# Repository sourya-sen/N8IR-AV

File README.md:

The N8IR is a standalone experimental audiovisual synthesizer and phrase generator. Designed with a simple set of interconnected audio and visual controls and a modular patchbay, the N8IR creates tightly synced audiovisual patterns, powered by a Teensy microcontroller and CMOS logic chips.

Detailed manual and documentation to follow.

This project would not be possible without the knowledge shared on the electro-music forums and previous work by Andy Murkin.

More on Lunetta Synthesis: https://hackaday.com/series_of_posts/logic-noise/ <br>
The Melody Generator Circuit on the electro-music forums: https://electro-music.com/forum/topic-42552.html<br>
Andy Murkin’s delay circuit: https://andymurkin.wordpress.com/2018/03/19/piezos-electrets-pt-4-electronics-and-a-very-very-simple-pt2399-echo-delay/<br>

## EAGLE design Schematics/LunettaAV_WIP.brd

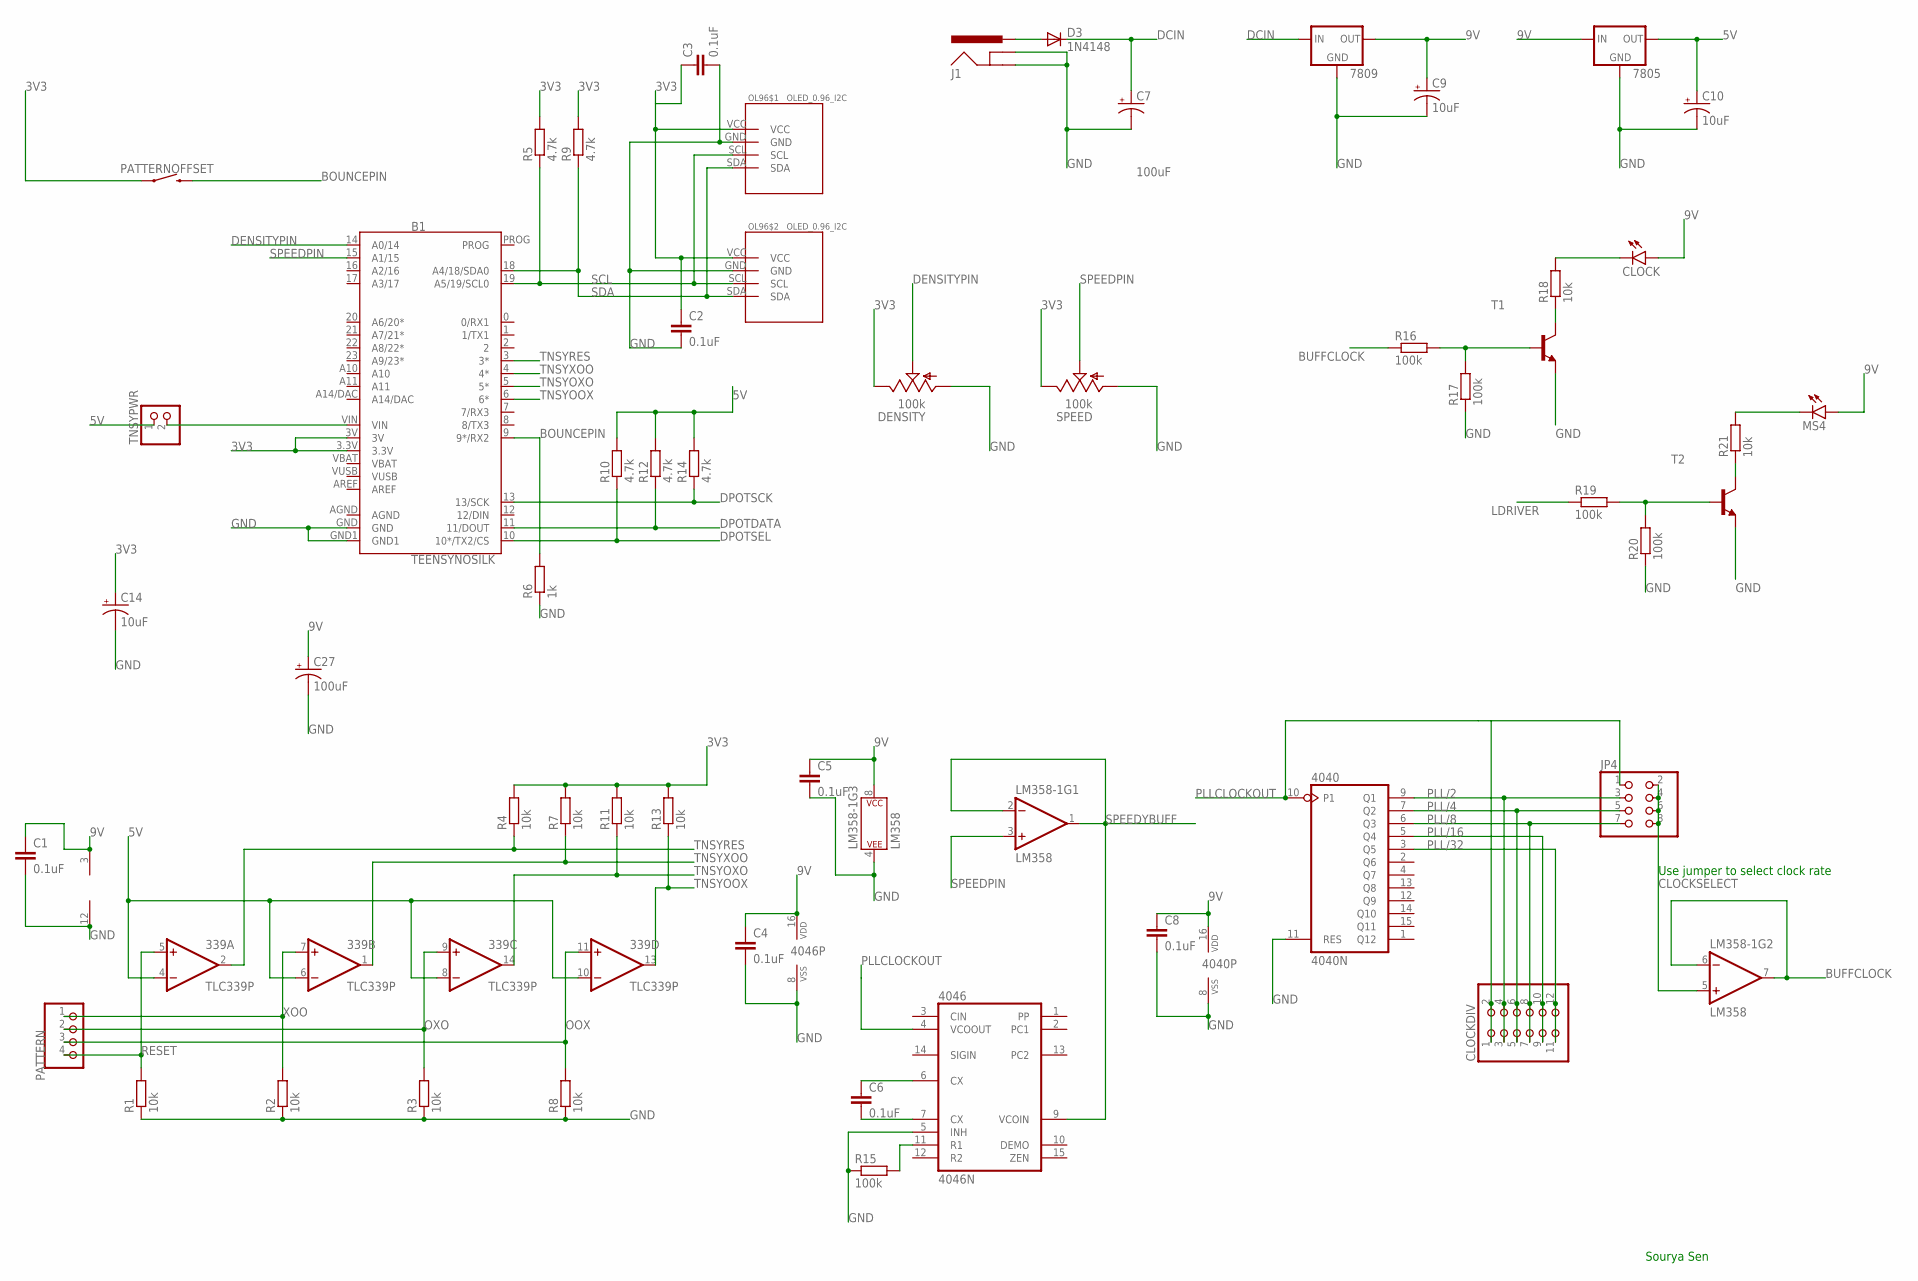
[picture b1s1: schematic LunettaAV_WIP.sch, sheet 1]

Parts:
339: TLC339P; DIL14
4040: 4040N; DIL16
4046: 4046N; DIL16
7805: 7805; 78XXS
7809: 7809; 78XXS
B1: TEENSYNOSILK; TEENSY_NOSILK
C1, C2, C3, C4, C5, C6, C8: 0.1uF; CAP-PTH-SMALL-KIT
C7, C27: 100uF; CPOL-RADIAL-2.5MM-6.5MM
C9, C10, C14: 10uF; CPOL-RADIAL-2.5MM-5MM
CLOCK: LED3MM; LED_3MM
CLOCKDIV: PINHD-2X6; 2X06
D3: 1N4148; DO35-7
DENSITY: 100k; 9MM_SNAP-IN_POT
J1: POWER_JACKPOWER_JACK_SLOT; POWER_JACK_PTH_SLOT
JP4: PINHD-2X4; 2X04
LM358-1: LM358; DIP08
MS4: LED3MM; LED_3MM
OL96$1, OL96$2: OLED_0.96_I2C
PATTERN: PINHD-1X4; 1X04
PATTERNOFFSET: MOMENTARY-SWITCH-SPST-PTH-12MM; TACTILE_SWITCH_PTH_12MM
R1, R2, R3, R4, R7, R8, R11, R13, R18, R21: 10k; 7MM_RESISTOR
R5, R9, R10, R12, R14: 4.7k; 7MM_RESISTOR
R6: 1k; 7MM_RESISTOR
R15, R16, R17, R19, R20: 100k; 7MM_RESISTOR
SPEED: 100k; 9MM_SNAP-IN_POT
T1, T2: 2N4401-NPN-TO92-EBC; TO92-EBC
TNSYPWR: PINHD-1X2; 1X02

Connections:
3V3: B1.3.3V, B1.3V, C2.1, C3.1, C14.1 (+), DENSITY.3 (E), OL96$1.VCC, OL96$2.VCC, PATTERNOFFSET.1, R4.2, R5.2, R7.2, R9.2, R11.2, R13.2, SPEED.3 (E)
5V: 339.4 (-IN), 339.6 (-IN), 339.8 (-IN), 339.10 (-IN), 7805.OUT, C10.1 (+), R10.2, R12.2, R14.2, TNSYPWR.1; also elsewhere on the board
9V: 339.3 (V+), 4040.16 (VDD), 4046.16 (VDD), 7805.IN, 7809.OUT, C1.1, C4.1, C5.1, C8.1, C9.1 (+), C27.1 (+), CLOCK.A, LM358-1.8 (P$V+), MS4.A; also elsewhere on the board
AGND: B1.AGND
BOUNCEPIN: B1.9 (9*/RX2), PATTERNOFFSET.3 (2), R6.2
BUFFCLOCK: LM358-1.6 (-IN), LM358-1.7 (OUT), R16.1; also elsewhere on the board
CLOCKSELECT: JP4.2, JP4.4, JP4.6, JP4.8, LM358-1.5 (+IN)
DCIN: 7809.IN, C7.1 (+), D3.C
DENSITYPIN: B1.14 (A0/14), DENSITY.2 (S)
DPOTDATA: B1.11 (11/DOUT), R12.1; also elsewhere on the board
DPOTSCK: B1.13 (13/SCK), R14.1; also elsewhere on the board
DPOTSEL: B1.10 (10*/TX2/CS), R10.1; also elsewhere on the board
GND: 339.12 (V-), 4040.8 (VSS), 4040.11 (RES), 4046.5 (INH), 4046.8 (VSS), 7805.GND, 7809.GND, B1.GND, B1.GND1, C1.2, C2.2, C3.2, C4.2, C5.2, C7.2 (-), C8.2, C9.2 (-), C10.2 (-), C14.2 (-), C27.2 (-), DENSITY.1 (A), J1.GND, J1.GNDBREAK, LM358-1.4 (P$V-), OL96$1.GND, OL96$2.GND, R1.1, R2.1, R3.1, R6.1, R8.1, R15.1, R17.1, R20.1, SPEED.1 (A), T1.E, T2.E; also elsewhere on the board
LDRIVER: R19.1; also elsewhere on the board
unnamed: B1.VIN, TNSYPWR.2
unnamed: 4046.7 (CX), C6.2
unnamed: 4046.6 (CX), C6.1
unnamed: 4046.11 (R1), R15.2
unnamed: R16.2, R17.2, T1.B
unnamed: R18.1, T1.C
unnamed: CLOCK.K (C), R18.2
unnamed: R19.2, R20.2, T2.B
unnamed: R21.1, T2.C
unnamed: MS4.K (C), R21.2
unnamed: D3.A, J1.PWR
OOX: 339.11 (+IN), PATTERN.3, R8.2
OXO: 339.9 (+IN), PATTERN.2, R3.2
PLL/2: 4040.9 (Q1), CLOCKDIV.3, CLOCKDIV.4, JP4.3
PLL/4: 4040.7 (Q2), CLOCKDIV.5, CLOCKDIV.6, JP4.5
PLL/8: 4040.6 (Q3), CLOCKDIV.7, CLOCKDIV.8, JP4.7
PLL/16: 4040.5 (Q4), CLOCKDIV.9, CLOCKDIV.10
PLL/32: 4040.3 (Q5), CLOCKDIV.11, CLOCKDIV.12
PLLCLOCKOUT: 4040.10 (P1), 4046.4 (VCOOUT), CLOCKDIV.1, CLOCKDIV.2, JP4.1
RESET: 339.5 (+IN), PATTERN.4, R1.2
SCL: B1.19 (A5/19/SCL0), OL96$1.SCL, OL96$2.SCL, R5.1
SDA: B1.18 (A4/18/SDA0), OL96$1.SDA, OL96$2.SDA, R9.1
SPEEDPIN: B1.15 (A1/15), LM358-1.3 (+IN), SPEED.2 (S)
SPEEDYBUFF: 4046.9 (VCOIN), LM358-1.1 (OUT), LM358-1.2 (-IN)
TNSYOOX: 339.13 (OUT), B1.6 (6*), R13.1
TNSYOXO: 339.14 (OUT), B1.5 (5*), R11.1
TNSYRES: 339.2 (OUT), B1.3 (3*), R4.1
TNSYXOO: 339.1 (OUT), B1.4 (4*), R7.1
VBAT: B1.VBAT
VUSB: B1.VUSB
XOO: 339.7 (+IN), PATTERN.1, R2.2

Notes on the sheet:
Use jumper to select clock rate
Sourya Sen

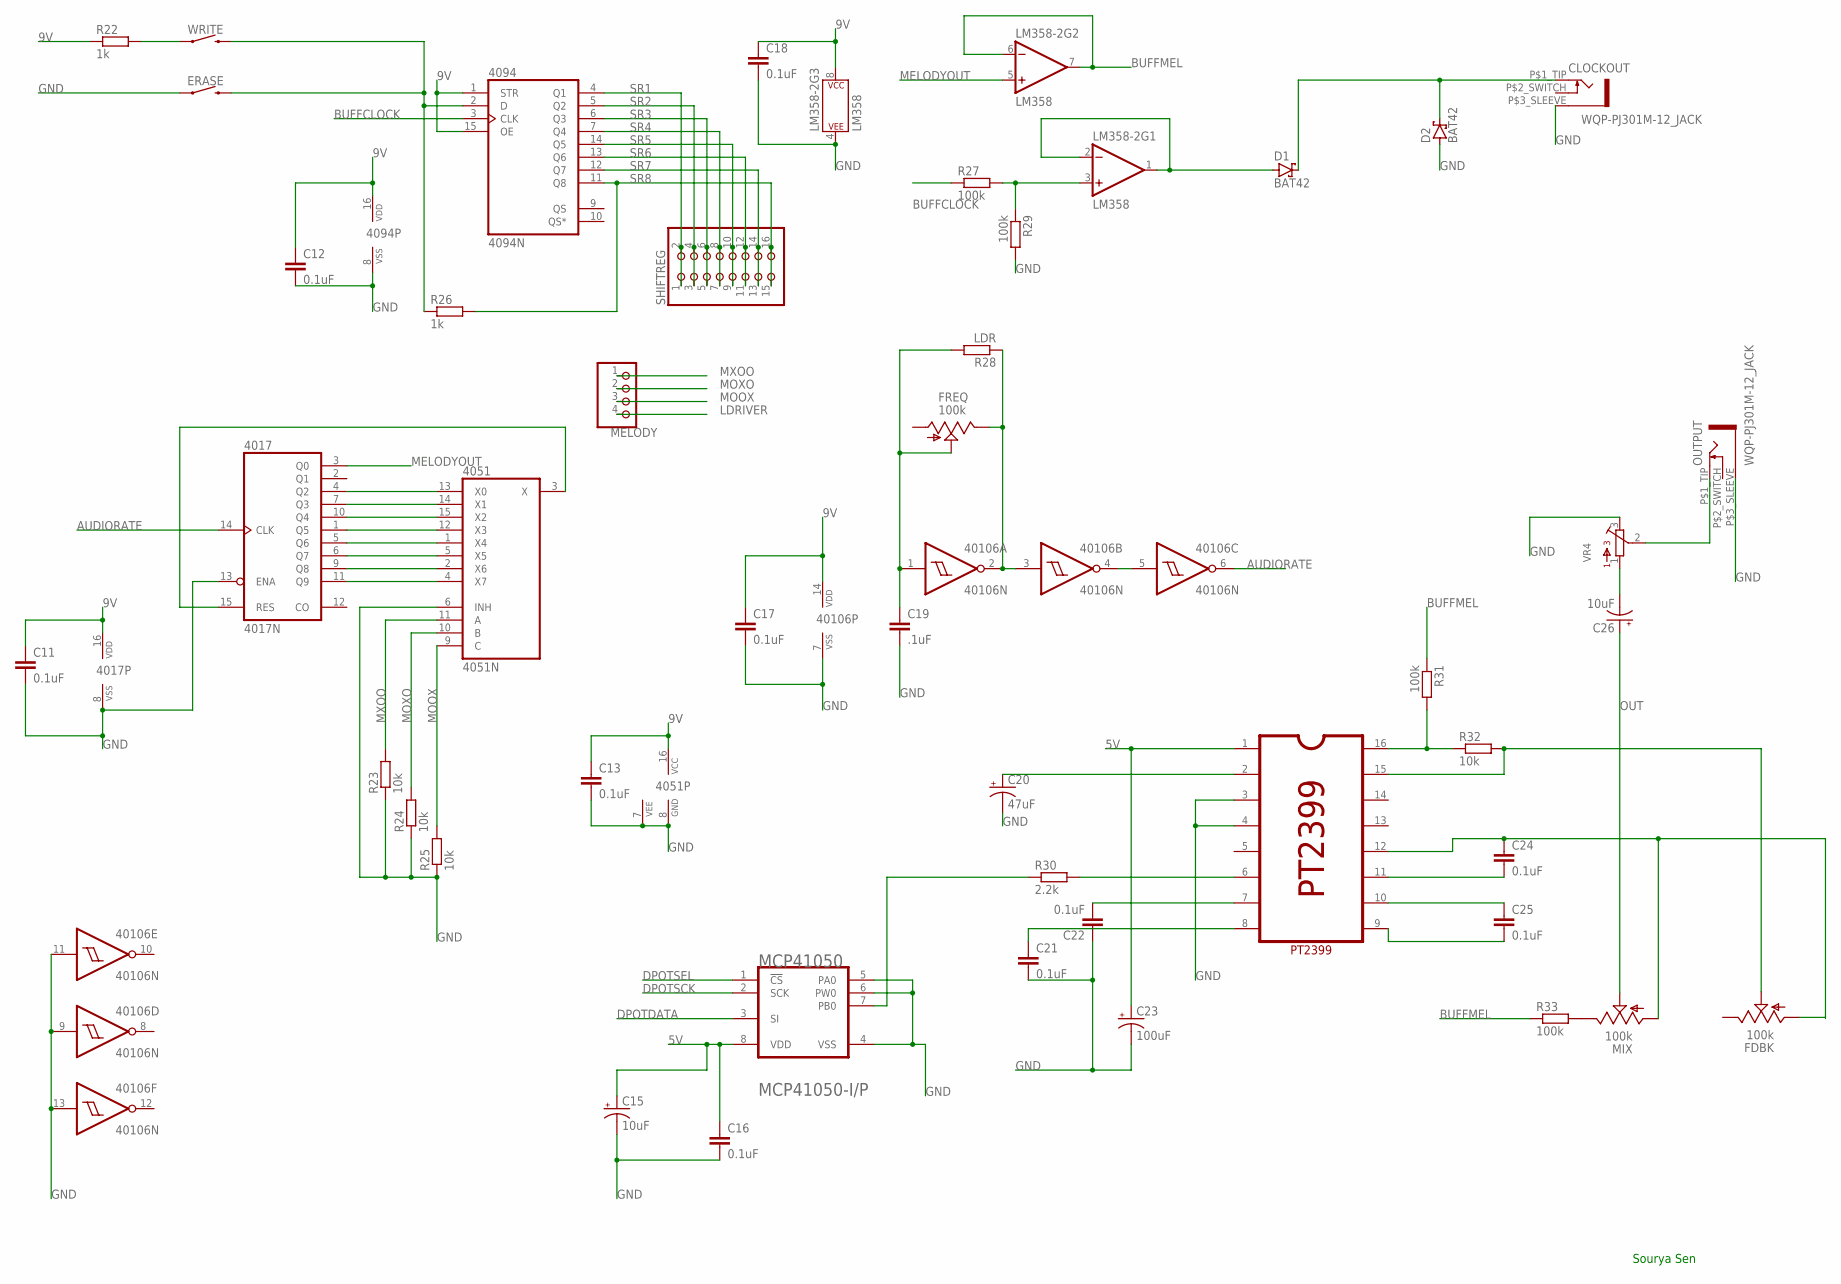
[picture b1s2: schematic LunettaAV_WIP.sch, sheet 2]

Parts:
4017: 4017N; DIL16
4051: 4051N; DIL16
4094: 4094N; DIL16
40106: 40106N; DIL14
C11, C12, C13, C16, C17, C18, C21, C22, C24, C25: 0.1uF; CAP-PTH-SMALL-KIT
C15, C26: 10uF; CPOL-RADIAL-2.5MM-5MM
C19: .1uF; C5B3.5
C20: 47uF; CPOL-RADIAL-2.5MM-5MM
C23: 100uF; CPOL-RADIAL-2.5MM-6.5MM
CLOCKOUT: WQP-PJ301M-12_JACK
D1, D2: BAT42; DO35-10
ERASE: MOMENTARY-SWITCH-SPST-PTH-12MM; TACTILE_SWITCH_PTH_12MM
FDBK: 100k; 9MM_SNAP-IN_POT
FREQ: 100k; 9MM_SNAP-IN_POT
LM358-2: LM358; DIP08
MCP41050: MCP41050; MICROCHIP_MCP41050-I-P_0
MELODY: PINHD-1X4; 1X04
MIX: 100k; 9MM_SNAP-IN_POT
OUTPUT: WQP-PJ301M-12_JACK
PT2399: PT2399; DIP-16
R22, R26: 1k; 7MM_RESISTOR
R23, R24, R25, R32: 10k; 7MM_RESISTOR
R27, R29, R31, R33: 100k; 7MM_RESISTOR
R28: LDR; 0204V
R30: 2.2k; 7MM_RESISTOR
SHIFTREG: PINHD-2X8; 2X08
VR4: BOURNS_3362P_TRIMMERP; BOURNS_3362P_TRIMMER
WRITE: MOMENTARY-SWITCH-SPST-PTH-12MM; TACTILE_SWITCH_PTH_12MM

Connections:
5V: C15.1 (+), C16.1, C23.1 (+), MCP41050.8 (VDD), PT2399.1; also elsewhere on the board
9V: 4017.16 (VDD), 4051.16 (VCC), 4094.1 (STR), 4094.15 (OE), 4094.16 (VDD), 40106.14 (VDD), C11.1, C12.1, C13.1, C17.1, C18.1, LM358-2.8 (P$V+), R22.1; also elsewhere on the board
AUDIORATE: 4017.14 (CLK), 40106.6 (O)
BUFFCLOCK: 4094.3 (CLK), R27.1; also elsewhere on the board
BUFFMEL: LM358-2.6 (-IN), LM358-2.7 (OUT), R31.1, R33.1
DPOTDATA: MCP41050.3 (SI); also elsewhere on the board
DPOTSCK: MCP41050.2 (SCK); also elsewhere on the board
DPOTSEL: MCP41050.1 (!CS!); also elsewhere on the board
GND: 4017.8 (VSS), 4017.13 (ENA), 4051.6 (INH), 4051.7 (VEE), 4051.8 (GND), 4094.8 (VSS), 40106.7 (VSS), 40106.9 (I), 40106.11 (I), 40106.13 (I), C11.2, C12.2, C13.2, C15.2 (-), C16.2, C17.2, C18.2, C19.2, C20.2 (-), C21.2, C22.1, C23.2 (-), CLOCKOUT.P$3_SLEEVE (1), D2.A, ERASE.1, LM358-2.4 (P$V-), MCP41050.4 (VSS), MCP41050.5 (PA0), MCP41050.6 (PW0), OUTPUT.P$3_SLEEVE (1), PT2399.3, PT2399.4, R23.1, R24.1, R25.1, R29.2, VR4.3; also elsewhere on the board
LDRIVER: MELODY.4; also elsewhere on the board
MELODYOUT: 4017.3 (Q0), LM358-2.5 (+IN)
MOOX: 4051.9 (C), MELODY.3, R25.2
MOXO: 4051.10 (B), MELODY.2, R24.2
MXOO: 4051.11 (A), MELODY.1, R23.2
unnamed: C24.1, FDBK.1 (A), MIX.1 (A), PT2399.12
unnamed: MIX.3 (E), R33.2
unnamed: C25.2, PT2399.9
unnamed: R22.2, WRITE.1
unnamed: 40106.2 (O), 40106.3 (I), FREQ.3 (E), R28.1
unnamed: 40106.4 (O), 40106.5 (I)
unnamed: 40106.1 (I), C19.1, FREQ.2 (S), R28.2
unnamed: C25.1, PT2399.10
unnamed: LM358-2.3 (+IN), R27.2, R29.1
unnamed: D1.A, LM358-2.1 (OUT), LM358-2.2 (-IN)
unnamed: PT2399.6, R30.2
unnamed: C20.1 (+), PT2399.2
unnamed: C22.2, PT2399.7
unnamed: C21.1, PT2399.8
unnamed: 4017.15 (RES), 4051.3 (X)
unnamed: 4017.4 (Q2), 4051.13 (X0)
unnamed: 4017.7 (Q3), 4051.14 (X1)
unnamed: 4017.10 (Q4), 4051.15 (X2)
unnamed: 4017.1 (Q5), 4051.12 (X3)
unnamed: 4017.5 (Q6), 4051.1 (X4)
unnamed: 4017.6 (Q7), 4051.5 (X5)
unnamed: 4017.9 (Q8), 4051.2 (X6)
unnamed: 4017.11 (Q9), 4051.4 (X7)
unnamed: 4094.2 (D), ERASE.3 (2), R26.1, WRITE.3 (2)
unnamed: PT2399.16, R31.2, R32.1
unnamed: FDBK.2 (S), PT2399.15, R32.2
unnamed: C24.2, PT2399.11
unnamed: CLOCKOUT.P$1_TIP (2), D1.C, D2.C
unnamed: MCP41050.7 (PB0), R30.1
unnamed: OUTPUT.P$1_TIP (2), VR4.2
unnamed: C26.2 (-), VR4.1
OUT: C26.1 (+), MIX.2 (S)
SR1: 4094.4 (Q1), SHIFTREG.1, SHIFTREG.2
SR2: 4094.5 (Q2), SHIFTREG.3, SHIFTREG.4
SR3: 4094.6 (Q3), SHIFTREG.5, SHIFTREG.6
SR4: 4094.7 (Q4), SHIFTREG.7, SHIFTREG.8
SR5: 4094.14 (Q5), SHIFTREG.9, SHIFTREG.10
SR6: 4094.13 (Q6), SHIFTREG.11, SHIFTREG.12
SR7: 4094.12 (Q7), SHIFTREG.13, SHIFTREG.14
SR8: 4094.11 (Q8), R26.2, SHIFTREG.15, SHIFTREG.16

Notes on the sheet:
Sourya Sen

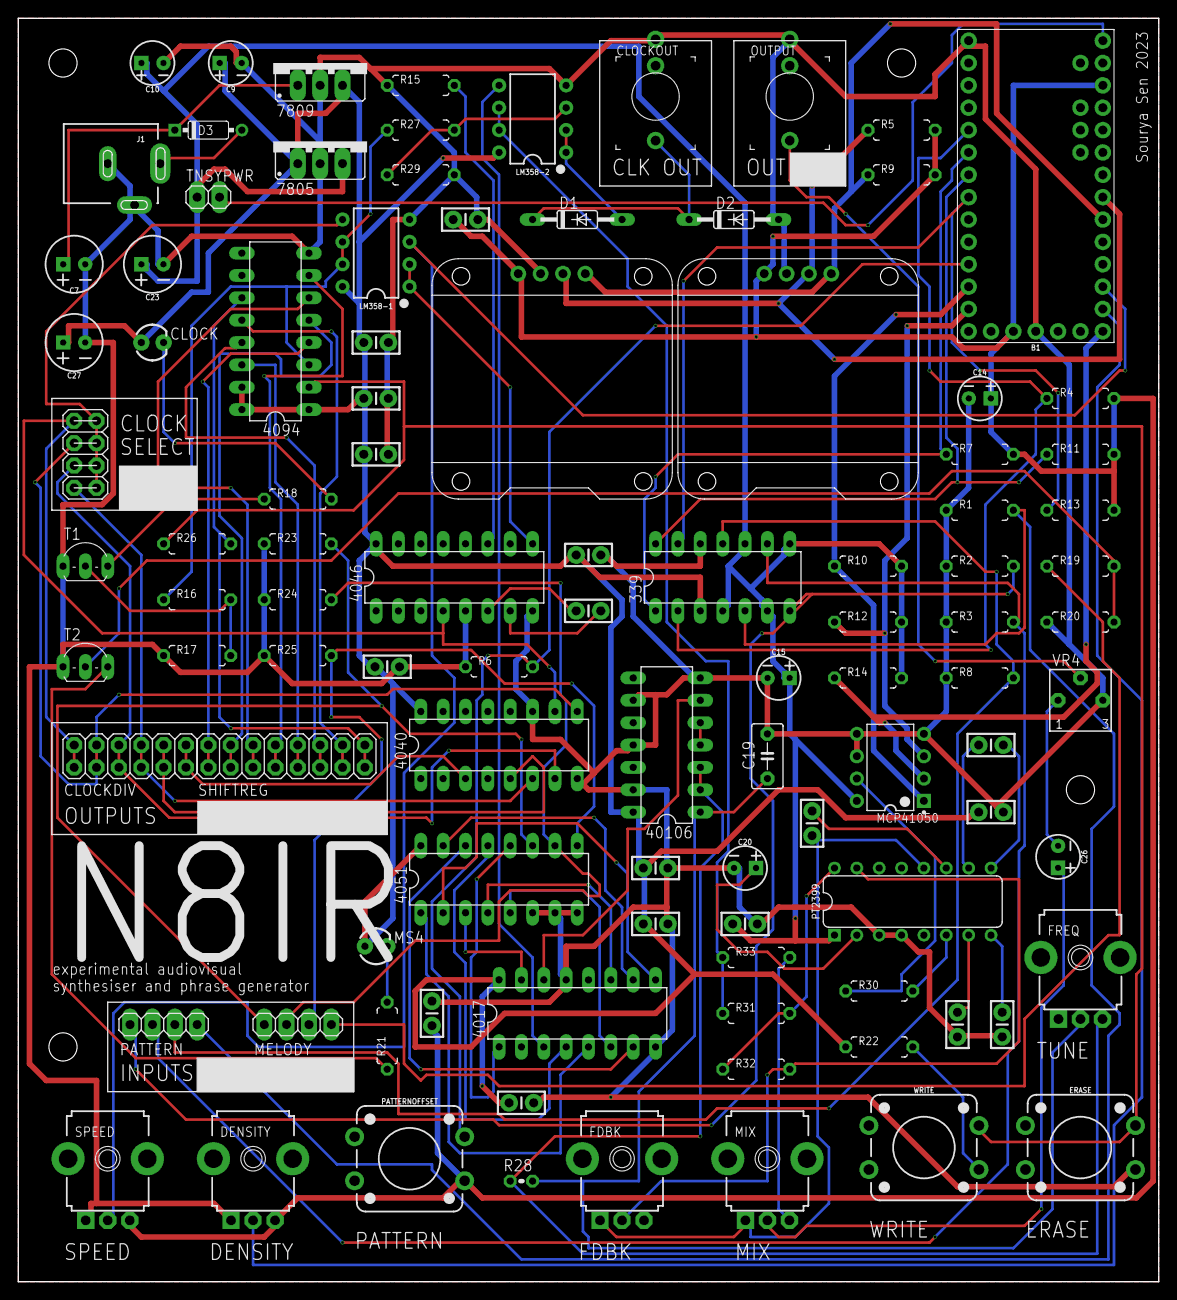
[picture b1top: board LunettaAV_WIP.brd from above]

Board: 2 copper layers, 129.5 x 143.5 mm, 105 parts (0 on the bottom side), 88 nets.

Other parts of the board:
U$1, U$2, U$3, U$4: MOUNTING_HOLE

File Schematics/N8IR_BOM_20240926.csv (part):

"Part";"Value";"Device";"Package";"Description";"CIIVA_IDS";"CODE__JEDEC";"COMPONENT_LINK_1_DESCRIPTION";"COMPONENT_LINK_1_URL";"COMPONENT_LINK_3_DESCRIPTION";"COMPONENT_LINK_3_URL";"DATASHEET";"DATASHEET_VERSION";"FOOTPRINT_VARIANT_NAME_0";"IMPORTED";"IMPORTED_FROM";"IMPORT_TS";"MF";"MPN";"PACKAGE";"PACKAGE_DESCRIPTION";"PACKAGE_VERSION";"PIN_0_0_3_INSIDE_EDGE";"POPULARITY";"PREFIX";"PROD_ID";"RELEASE_DATE";"SF_ID";"SF_SKU";"SPICEPREFIX";"VALUE";"VAULT_GUID";"VAULT_REVISION";
"339";"TLC339P";"TLC339P";"DIL14";"COMPARATOR";"";"";"";"";"";"";"";"";"";"";"";"";"";"";"";"";"";"";"3";"";"";"";"";"";"";"";"";"";
"4017";"4017N";"4017N";"DIL16";"COUNTER/DIVIDER";"";"";"";"";"";"";"";"";"";"";"";"";"";"";"";"";"";"";"2";"";"";"";"";"";"";"";"";"";
"4040";"4040N";"4040N";"DIL16";"12-stage binary/ripple COUNTER";"";"";"";"";"";"";"";"";"";"";"";"";"";"";"";"";"";"";"2";"";"";"";"";"";"";"";"";"";
"4046";"4046N";"4046N";"DIL16";"Micropower PLL";"";"";"";"";"";"";"";"";"";"";"";"";"";"";"";"";"";"";"1";"";"";"";"";"";"";"";"";"";
"4051";"4051N";"4051N";"DIL16";"8-channel ANALOG MULTIPLEXER";"";"";"";"";"";"";"";"";"";"";"";"";"";"";"";"";"";"";"15";"";"";"";"";"";"";"";"";"";
"4094";"4094N";"4094N";"DIL16";"8-stage SHIFT/STORE REGISTER, tri-state";"";"";"";"";"";"";"";"";"";"";"";"";"";"";"";"";"";"";"1";"";"";"";"";"";"";"";"";"";
"7805";"7805";"78XXS";"78XXS";"VOLTAGE REGULATOR";"";"";"";"";"";"";"";"";"";"";"";"";"";"";"";"";"";"";"18";"";"";"";"";"";"";"";"";"";
"7809";"7809";"78XXS";"78XXS";"VOLTAGE REGULATOR";"";"";"";"";"";"";"";"";"";"";"";"";"";"";"";"";"";"";"18";"";"";"";"";"";"";"";"";"";
"40106";"40106N";"40106N";"DIL14";"Hex SCHMITT TRIGGER";"";"";"";"";"";"";"";"";"";"";"";"";"";"";"";"";"";"";"4";"";"";"";"";"";"";"";"";"";
"B1";"TEENSYNOSILK";"TEENSYNOSILK";"TEENSY_NOSILK";"Teensy Footprint";"";"";"";"";"";"";"";"";"";"";"";"";"";"";"";"";"";"";"";"";"";"";"DEV-12646";"";"";"";"";"";
"C1";"0.1uF";"0.1UF-KIT-EZ-50V-20%";"CAP-PTH-SMALL-KIT";"0.1µF ceramic capacitors";"";"";"";"";"";"";"";"";"";"";"";"";"";"";"";"";"";"";"";"";"CAP-08370";"";"";"";"";"0.1uF";"";"";
"C2";"0.1uF";"0.1UF-KIT-EZ-50V-20%";"CAP-PTH-SMALL-KIT";"0.1µF ceramic capacitors";"";"";"";"";"";"";"";"";"";"";"";"";"";"";"";"";"";"";"";"";"CAP-08370";"";"";"";"";"0.1uF";"";"";
"C3";"0.1uF";"0.1UF-KIT-EZ-50V-20%";"CAP-PTH-SMALL-KIT";"0.1µF ceramic capacitors";"";"";"";"";"";"";"";"";"";"";"";"";"";"";"";"";"";"";"";"";"CAP-08370";"";"";"";"";"0.1uF";"";"";
"C4";"0.1uF";"0.1UF-KIT-EZ-50V-20%";"CAP-PTH-SMALL-KIT";"0.1µF ceramic capacitors";"";"";"";"";"";"";"";"";"";"";"";"";"";"";"";"";"";"";"";"";"CAP-08370";"";"";"";"";"0.1uF";"";"";
"C5";"0.1uF";"0.1UF-KIT-EZ-50V-20%";"CAP-PTH-SMALL-KIT";"0.1µF ceramic capacitors";"";"";"";"";"";"";"";"";"";"";"";"";"";"";"";"";"";"";"";"";"CAP-08370";"";"";"";"";"0.1uF";"";"";
"C6";"0.1uF";"0.1UF-KIT-EZ-50V-20%";"CAP-PTH-SMALL-KIT";"0.1µF ceramic capacitors";"";"";"";"";"";"";"";"";"";"";"";"";"";"";"";"";"";"";"";"";"CAP-08370";"";"";"";"";"0.1uF";"";"";
"C7";"100uF";"100UF-POLAR-RADIAL-2.5MM-25V-20%";"CPOL-RADIAL-2.5MM-6.5MM";"100µF polarized capacitors";"";"";"";"";"";"";"";"";"";"";"";"";"";"";"";"";"";"";"";"";"CAP-08439";"";"";"";"";"100uF";"";"";
"C8";"0.1uF";"0.1UF-KIT-EZ-50V-20%";"CAP-PTH-SMALL-KIT";"0.1µF ceramic capacitors";"";"";"";"";"";"";"";"";"";"";"";"";"";"";"";"";"";"";"";"";"CAP-08370";"";"";"";"";"0.1uF";"";"";
"C9";"10uF";"10UF-POLAR-RADIAL-2.5MM-25V-20%";"CPOL-RADIAL-2.5MM-5MM";"10.0µF polarized capacitors";"";"";"";"";"";"";"";"";"";"";"";"";"";"";"";"";"";"";"";"";"CAP-08440";"";"";"";"";"10uF";"";"";
"C10";"10uF";"10UF-POLAR-RADIAL-2.5MM-25V-20%";"CPOL-RADIAL-2.5MM-5MM";"10.0µF polarized capacitors";"";"";"";"";"";"";"";"";"";"";"";"";"";"";"";"";"";"";"";"";"CAP-08440";"";"";"";"";"10uF";"";"";
"C11";"0.1uF";"0.1UF-KIT-EZ-50V-20%";"CAP-PTH-SMALL-KIT";"0.1µF ceramic capacitors";"";"";"";"";"";"";"";"";"";"";"";"";"";"";"";"";"";"";"";"";"CAP-08370";"";"";"";"";"0.1uF";"";"";
"C12";"0.1uF";"0.1UF-KIT-EZ-50V-20%";"CAP-PTH-SMALL-KIT";"0.1µF ceramic capacitors";"";"";"";"";"";"";"";"";"";"";"";"";"";"";"";"";"";"";"";"";"CAP-08370";"";"";"";"";"0.1uF";"";"";
"C13";"0.1uF";"0.1UF-KIT-EZ-50V-20%";"CAP-PTH-SMALL-KIT";"0.1µF ceramic capacitors";"";"";"";"";"";"";"";"";"";"";"";"";"";"";"";"";"";"";"";"";"CAP-08370";"";"";"";"";"0.1uF";"";"";
"C14";"10uF";"10UF-POLAR-RADIAL-2.5MM-25V-20%";"CPOL-RADIAL-2.5MM-5MM";"10.0µF polarized capacitors";"";"";"";"";"";"";"";"";"";"";"";"";"";"";"";"";"";"";"";"";"CAP-08440";"";"";"";"";"10uF";"";"";
"C15";"10uF";"10UF-POLAR-RADIAL-2.5MM-25V-20%";"CPOL-RADIAL-2.5MM-5MM";"10.0µF polarized capacitors";"";"";"";"";"";"";"";"";"";"";"";"";"";"";"";"";"";"";"";"";"CAP-08440";"";"";"";"";"10uF";"";"";
"C16";"0.1uF";"0.1UF-KIT-EZ-50V-20%";"CAP-PTH-SMALL-KIT";"0.1µF ceramic capacitors";"";"";"";"";"";"";"";"";"";"";"";"";"";"";"";"";"";"";"";"";"CAP-08370";"";"";"";"";"0.1uF";"";"";
"C17";"0.1uF";"0.1UF-KIT-EZ-50V-20%";"CAP-PTH-SMALL-KIT";"0.1µF ceramic capacitors";"";"";"";"";"";"";"";"";"";"";"";"";"";"";"";"";"";"";"";"";"CAP-08370";"";"";"";"";"0.1uF";"";"";
"C18";"0.1uF";"0.1UF-KIT-EZ-50V-20%";"CAP-PTH-SMALL-KIT";"0.1µF ceramic capacitors";"";"";"";"";"";"";"";"";"";"";"";"";"";"";"";"";"";"";"";"";"CAP-08370";"";"";"";"";"0.1uF";"";"";
"C19";".1uF";"C5/3.5";"C5B3.5";"CAPACITOR";"";"";"";"";"";"";"";"";"";"";"";"";"";"";"";"";"";"";"3";"";"";"";"";"";"";"";"";"";
"C20";"47uF";"10UF-POLAR-RADIAL-2.5MM-25V-20%";"CPOL-RADIAL-2.5MM-5MM";"10.0µF polarized capacitors";"";"";"";"";"";"";"";"";"";"";"";"";"";"";"";"";"";"";"";"";"CAP-08440";"";"";"";"";"10uF";"";"";
"C21";"0.1uF";"0.1UF-KIT-EZ-50V-20%";"CAP-PTH-SMALL-KIT";"0.1µF ceramic capacitors";"";"";"";"";"";"";"";"";"";"";"";"";"";"";"";"";"";"";"";"";"CAP-08370";"";"";"";"";"0.1uF";"";"";
"C22";"0.1uF";"0.1UF-KIT-EZ-50V-20%";"CAP-PTH-SMALL-KIT";"0.1µF ceramic capacitors";"";"";"";"";"";"";"";"";"";"";"";"";"";"";"";"";"";"";"";"";"CAP-08370";"";"";"";"";"0.1uF";"";"";
"C23";"100uF";"100UF-POLAR-RADIAL-2.5MM-25V-20%";"CPOL-RADIAL-2.5MM-6.5MM";"100µF polarized capacitors";"";"";"";"";"";"";"";"";"";"";"";"";"";"";"";"";"";"";"";"";"CAP-08439";"";"";"";"";"100uF";"";"";
"C24";"0.1uF";"0.1UF-KIT-EZ-50V-20%";"CAP-PTH-SMALL-KIT";"0.1µF ceramic capacitors";"";"";"";"";"";"";"";"";"";"";"";"";"";"";"";"";"";"";"";"";"CAP-08370";"";"";"";"";"0.1uF";"";"";
"C25";"0.1uF";"0.1UF-KIT-EZ-50V-20%";"CAP-PTH-SMALL-KIT";"0.1µF ceramic capacitors";"";"";"";"";"";"";"";"";"";"";"";"";"";"";"";"";"";"";"";"";"CAP-08370";"";"";"";"";"0.1uF";"";"";
"C26";"10uF";"10UF-POLAR-RADIAL-2.5MM-25V-20%";"CPOL-RADIAL-2.5MM-5MM";"10.0µF polarized capacitors";"";"";"";"";"";"";"";"";"";"";"";"";"";"";"";"";"";"";"";"";"CAP-08440";"";"";"";"";"10uF";"";"";
"C27";"100uF";"100UF-POLAR-RADIAL-2.5MM-25V-20%";"CPOL-RADIAL-2.5MM-6.5MM";"100µF polarized capacitors";"";"";"";"";"";"";"";"";"";"";"";"";"";"";"";"";"";"";"";"";"CAP-08439";"";"";"";"";"100uF";"";"";
"CLOCK";"";"LED3MM";"LED_3MM";"LED (Generic)";"";"";"";"";"";"";"";"";"";"";"";"";"";"";"";"";"";"";"";"";"DIO-08794";"";"";"";"";"";"";"";
"CLOCKDIV";"";"PINHD-2X6";"2X06";"PIN HEADER";"";"";"";"";"";"";"";"";"";"";"";"";"";"";"";"";"";"";"8";"";"";"";"";"";"";"";"";"";
"CLOCKOUT";"WQP-PJ301M-12_JACK";"WQP-PJ301M-12_JACK";"WQP-PJ301M-12_JACK";"";"";"";"";"";"";"";"";"";"";"";"";"";"";"";"";"";"";"";"";"";"";"";"";"";"";"";"";"";
"D1";"BAT42";"BAT42";"DO35-10";"DIODE";"";"";"";"";"";"";"";"";"";"";"";"";"";"";"";"";"";"";"0";"";"";"";"";"";"";"";"";"";
"D2";"BAT42";"BAT42";"DO35-10";"DIODE";"";"";"";"";"";"";"";"";"";"";"";"";"";"";"";"";"";"";"0";"";"";"";"";"";"";"";"";"";
"D3";"1N4148";"SMALL_DIODEDO35-7";"DO35-7";"Small Signal Diode";"";"";"";"";"";"";"";"";"";"";"";"";"";"";"";"";"";"";"";"";"";"";"";"";"";"";"";"";
"DENSITY";"100k";"9MM_SNAP-IN_POT_";"9MM_SNAP-IN_POT";"9mm vertical snap-in pot, Alpha / Panasonic style";"";"";"";"";"";"";"";"";"";"";"";"";"";"";"";"";"";"";"";"";"";"";"";"";"";"";"";"";
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
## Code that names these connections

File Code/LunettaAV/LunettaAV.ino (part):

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};

//Pattern offset
int bouncePin = 9;
Bounce patternButton = Bounce(bouncePin, 5);
int patternOffset = 0;

//Pattern select input
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int pinOOOX = 6;

//Analog inputs
int densityPin = 14;
int speedPin = 15;

//Digipot
int slaveSelectPin = 10;
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  //Setup the I/O pins
  pinMode(13, OUTPUT); //SCK For Digipot.

  pinMode(bouncePin, INPUT); //this is for the button

  pinMode(densityPin, INPUT); //ANALOGINPUTS
  pinMode(speedPin, INPUT);

  pinMode(pinXOOO, INPUT);
  pinMode(pinOXOO, INPUT);
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    lastReset = XOOO;
  }

  int densityValue = analogRead(densityPin);
  _density = map(densityValue, 0, 1023, 1, DENSEMAX);

  int speedValue = analogRead(speedPin);
  _speed = map(speedValue, 0, 1023, 1, SPEEDMAX);

  Serial.print("_speed is: ");
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
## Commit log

2021-06-21 add WIP Teensy code
2021-06-21 add params to circle thing
2021-06-23 Initial commit schm for Teensy
2021-06-23 add EAGLE gitignore
2021-06-23 make schematics prettier
2021-06-23 fix analog input pins
2021-06-23 Add 358 and 4046 sections
2021-06-23 Add compartor section
2021-06-23 Teensy patternSelector + schematic fixes
2021-06-23 Change startup and reset functions
2021-06-24 refactor code and update square thing
2021-06-24 more cleanup
2021-06-24 some refactoring and organization of code
2021-06-24 Add 4094, 4017, 4040 and 4051 sections
2021-06-24 fix 4051 issues
2021-06-25 changes to schematics. brd file ignore for now.
2021-06-25 scehmatics fixes
2021-07-06 schematic updates
2021-07-09 more visuals and functions updated
2021-07-30 Add image
2023-03-27 fix 4017 schematics
2023-03-27 change melody out config and buffer the out for later stage
2023-03-28 PT2399 init + screen changed
2023-03-28 PT Delay and other fixes
2023-03-28 digipot working code
2023-03-28 fix Arduino code errors
2023-03-28 update schematics to match new code
2023-03-29 finish schematics?
2023-03-29 add more caps no cap
2023-03-29 code cleanups and parity among eagle and teensy naming schema
2023-03-29 brd init
2023-03-29 PCB Design
2023-03-29 redo routing
2023-03-29 fix minor schematic issues for a cleaner bom
2023-03-29 minor cleanups
2023-03-30 redesign board for mounting holes
2023-03-30 more changes and gerber for ordering
2023-04-12 fixes modifications and beautification for rev 2
2023-04-12 rev 2 routing
2023-07-31 v2 rc
2024-02-27 add two patterns
2024-02-27 add version number TODO: beautify code
2024-08-13 add todos
2024-08-13 fix md
2024-08-13 fix more md
2024-09-26 add gnd to 4040 res
2024-09-26 rev 2 updates
2024-09-26 add BOM
2024-09-26 README
2024-09-27 Rename Still 2024-09-27 154623_3.1.1.jpg to N8IRThumb
2024-09-27 Rename N8IRThumb to N8IRThumb.jpg
2024-09-27 Create LICENSE
2024-09-27 Add pdf schematics

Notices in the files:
parts and their libraries:
SparkFun-Boards: Licensing: Creative Commons ShareAlike 4.0 International - https://creativecommons.org/licenses/by-sa/4.0
